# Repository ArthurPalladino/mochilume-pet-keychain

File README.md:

# mochilume-pet-keychain
Um chaveiro interativo com um pet da raça mochilume dentro, feito com esp32, uma tela TFT e um módulo acelerômetro.

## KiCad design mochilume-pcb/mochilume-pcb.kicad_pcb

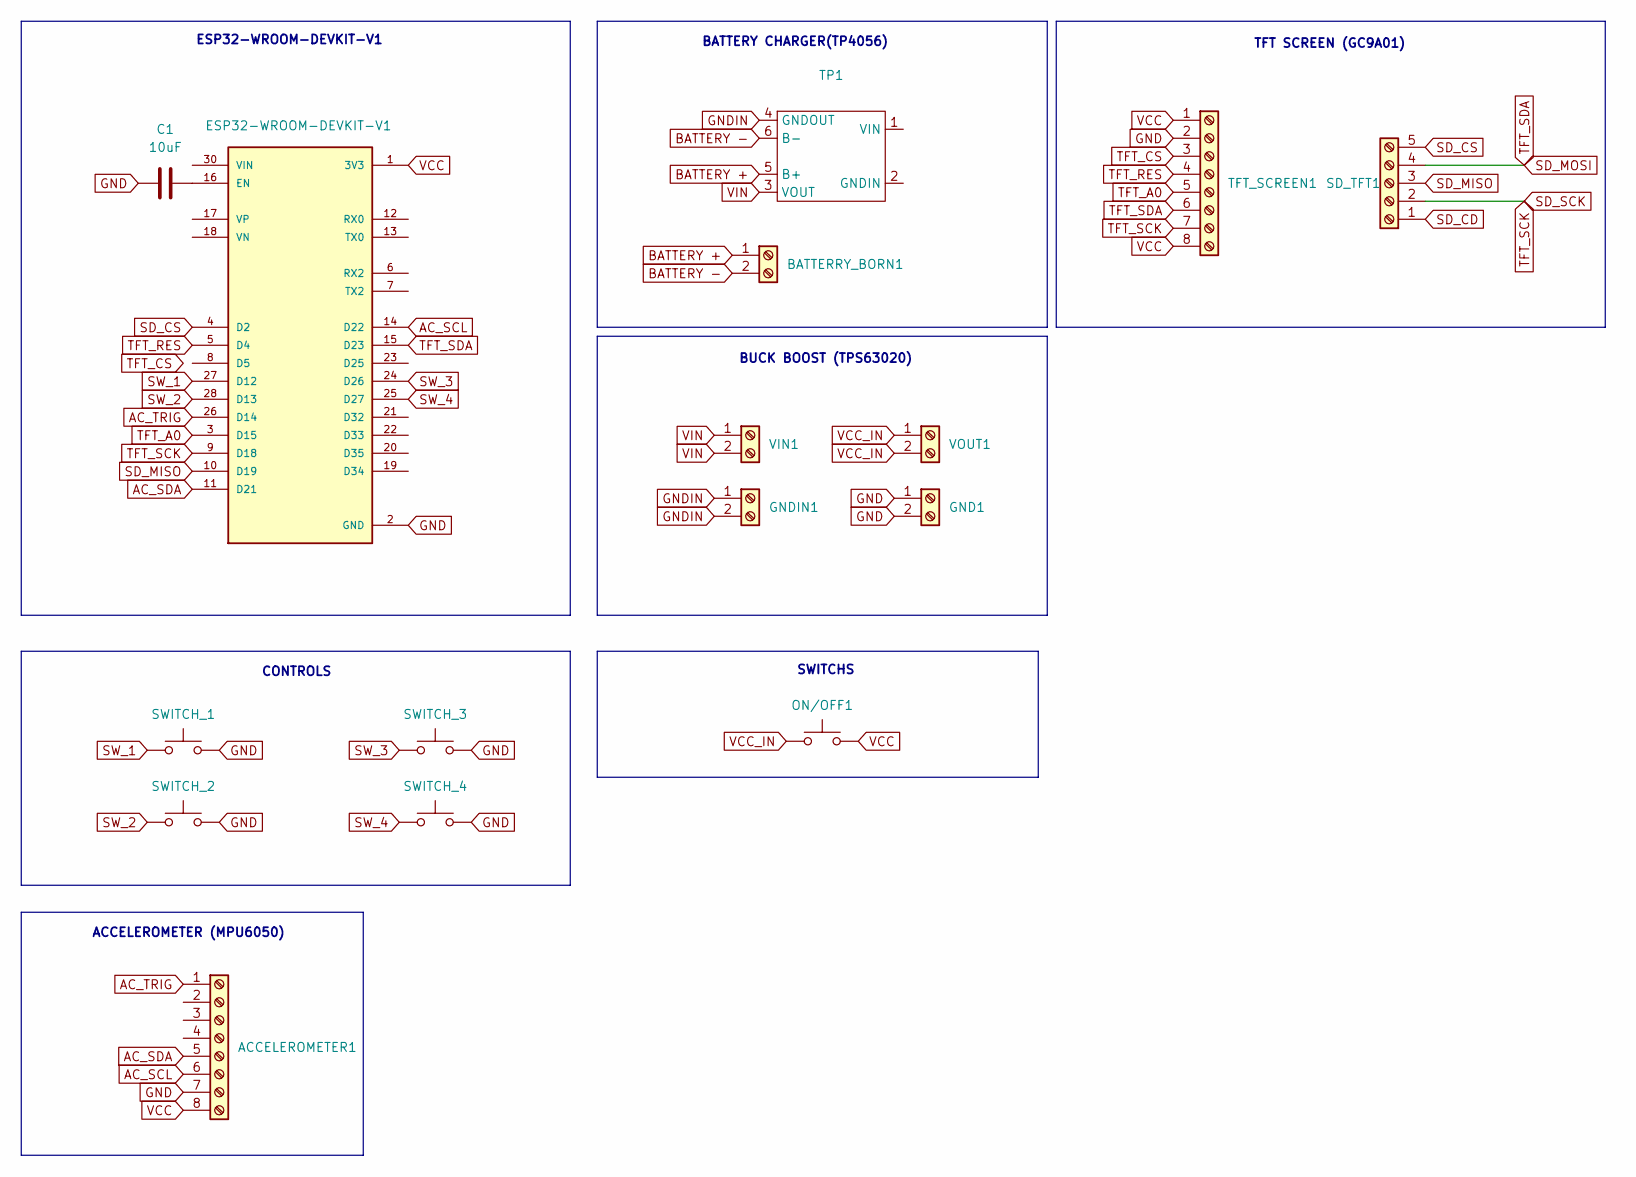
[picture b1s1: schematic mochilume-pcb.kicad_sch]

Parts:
ACCELEROMETER1: PinHeader_1x08_P2.54mm_Vertical
BATTERRY_BORN1: TerminalBlock_Phoenix_MKDS-1,5-2-5.08_1x02_P5.08mm_Horizont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
C1: 10uF; CP_Radial_D4.0mm_P2.00mm
ESP32-WROOM-DEVKIT-V1: MODULE_ESP32_DEVKIT_V1; PARTREV N/A
GND1: PinHeader_1x02_P2.54mm_Vertical
GNDIN1: PinHeader_1x02_P2.54mm_Vertical
ON/OFF1: TerminalBlock_Phoenix_MKDS-1,5-2-5.08_1x02_P5.08mm_Horizont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
SD_TFT1: PinHeader_1x05_P2.54mm_Vertical
SWITCH_1, SWITCH_2, SWITCH_3, SWITCH_4: SW_PUSH_6mm
TFT_SCREEN1: PinHeader_1x08_P2.54mm_Vertical
TP1: TP4056-18650
VIN1: PinHeader_1x02_P2.54mm_Vertical
VOUT1: PinHeader_1x02_P2.54mm_Vertical

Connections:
AC_SCL: ACCELEROMETER1.6, ESP32-WROOM-DEVKIT-V1.14 (D22)
AC_SDA: ACCELEROMETER1.5, ESP32-WROOM-DEVKIT-V1.11 (D21)
AC_TRIG: ACCELEROMETER1.1, ESP32-WROOM-DEVKIT-V1.26 (D14)
BATTERY +: BATTERRY_BORN1.1, TP1.5 (B+)
BATTERY -: BATTERRY_BORN1.2, TP1.6 (B-)
GND: ACCELEROMETER1.7, C1.1, ESP32-WROOM-DEVKIT-V1.2 (GND), ESP32-WROOM-DEVKIT-V1.29 (GND), GND1.1, GND1.2, SWITCH_1.2, SWITCH_2.2, SWITCH_3.2, SWITCH_4.2, TFT_SCREEN1.2
GNDIN: GNDIN1.1, GNDIN1.2, TP1.4 (GNDOUT)
unnamed: C1.2, ESP32-WROOM-DEVKIT-V1.16 (EN)
SD_CD: SD_TFT1.1
SD_CS: ESP32-WROOM-DEVKIT-V1.4 (D2), SD_TFT1.5
SD_MISO: ESP32-WROOM-DEVKIT-V1.10 (D19), SD_TFT1.3
SD_MOSI: ESP32-WROOM-DEVKIT-V1.15 (D23), SD_TFT1.4, TFT_SCREEN1.6
SD_SCK: ESP32-WROOM-DEVKIT-V1.9 (D18), SD_TFT1.2, TFT_SCREEN1.7
SW_1: ESP32-WROOM-DEVKIT-V1.27 (D12), SWITCH_1.1
SW_2: ESP32-WROOM-DEVKIT-V1.28 (D13), SWITCH_2.1
SW_3: ESP32-WROOM-DEVKIT-V1.24 (D26), SWITCH_3.1
SW_4: ESP32-WROOM-DEVKIT-V1.25 (D27), SWITCH_4.1
TFT_A0: ESP32-WROOM-DEVKIT-V1.3 (D15), TFT_SCREEN1.5
TFT_CS: TFT_SCREEN1.3
TFT_RES: ESP32-WROOM-DEVKIT-V1.5 (D4), TFT_SCREEN1.4
VCC: ACCELEROMETER1.8, ESP32-WROOM-DEVKIT-V1.1 (3V3), ON/OFF1.2, TFT_SCREEN1.1, TFT_SCREEN1.8
VCC_IN: ON/OFF1.1, VOUT1.1, VOUT1.2
VIN: TP1.3 (VOUT), VIN1.1, VIN1.2

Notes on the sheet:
CONTROLS
ACCELEROMETER (MPU6050)
SWITCHS
TFT SCREEN (GC9A01)
BUCK BOOST (TPS63020)
ESP32-WROOM-DEVKIT-V1
BATTERY CHARGER(TP4056)

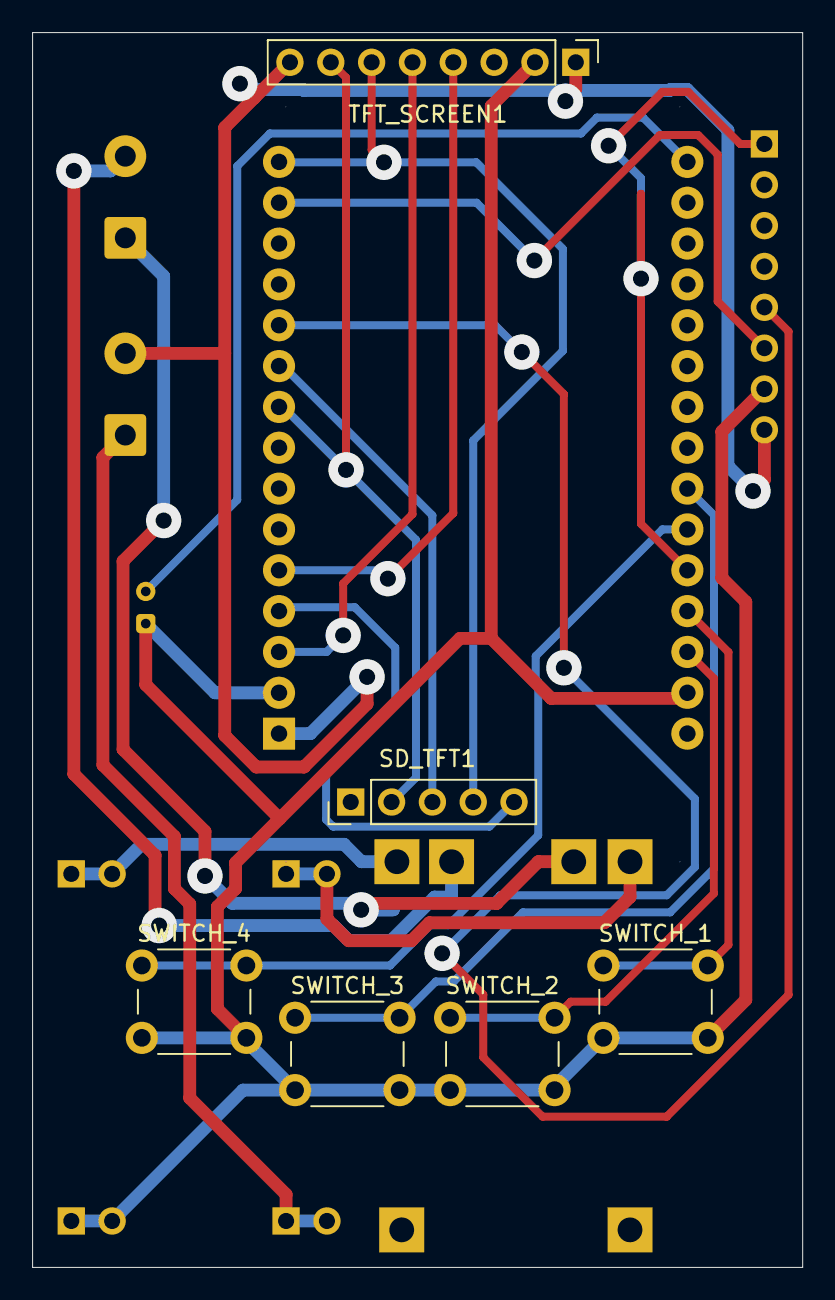
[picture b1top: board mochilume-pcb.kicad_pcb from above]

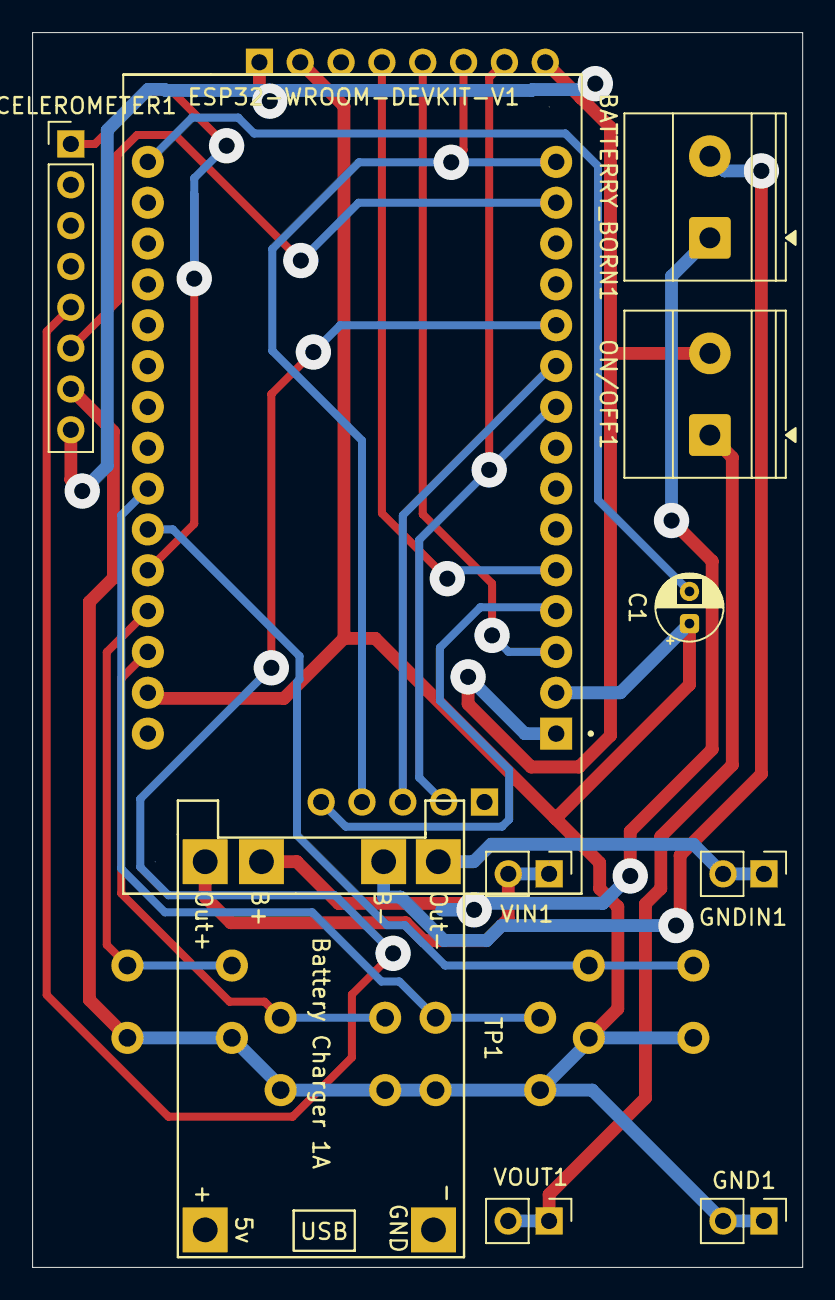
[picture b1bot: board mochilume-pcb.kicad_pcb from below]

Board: 2 copper layers, 47.9 x 76.8 mm, 16 parts (10 on the bottom side), 21 nets.

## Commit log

2026-01-08 feat: add mochilume pcb first version
2026-01-09 feat: assign footprints and trails to plate
2026-01-27 feat: add c++ project with platformio
